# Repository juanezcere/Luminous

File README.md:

# Luminous
This is a PDB design to show information in a luminous screen

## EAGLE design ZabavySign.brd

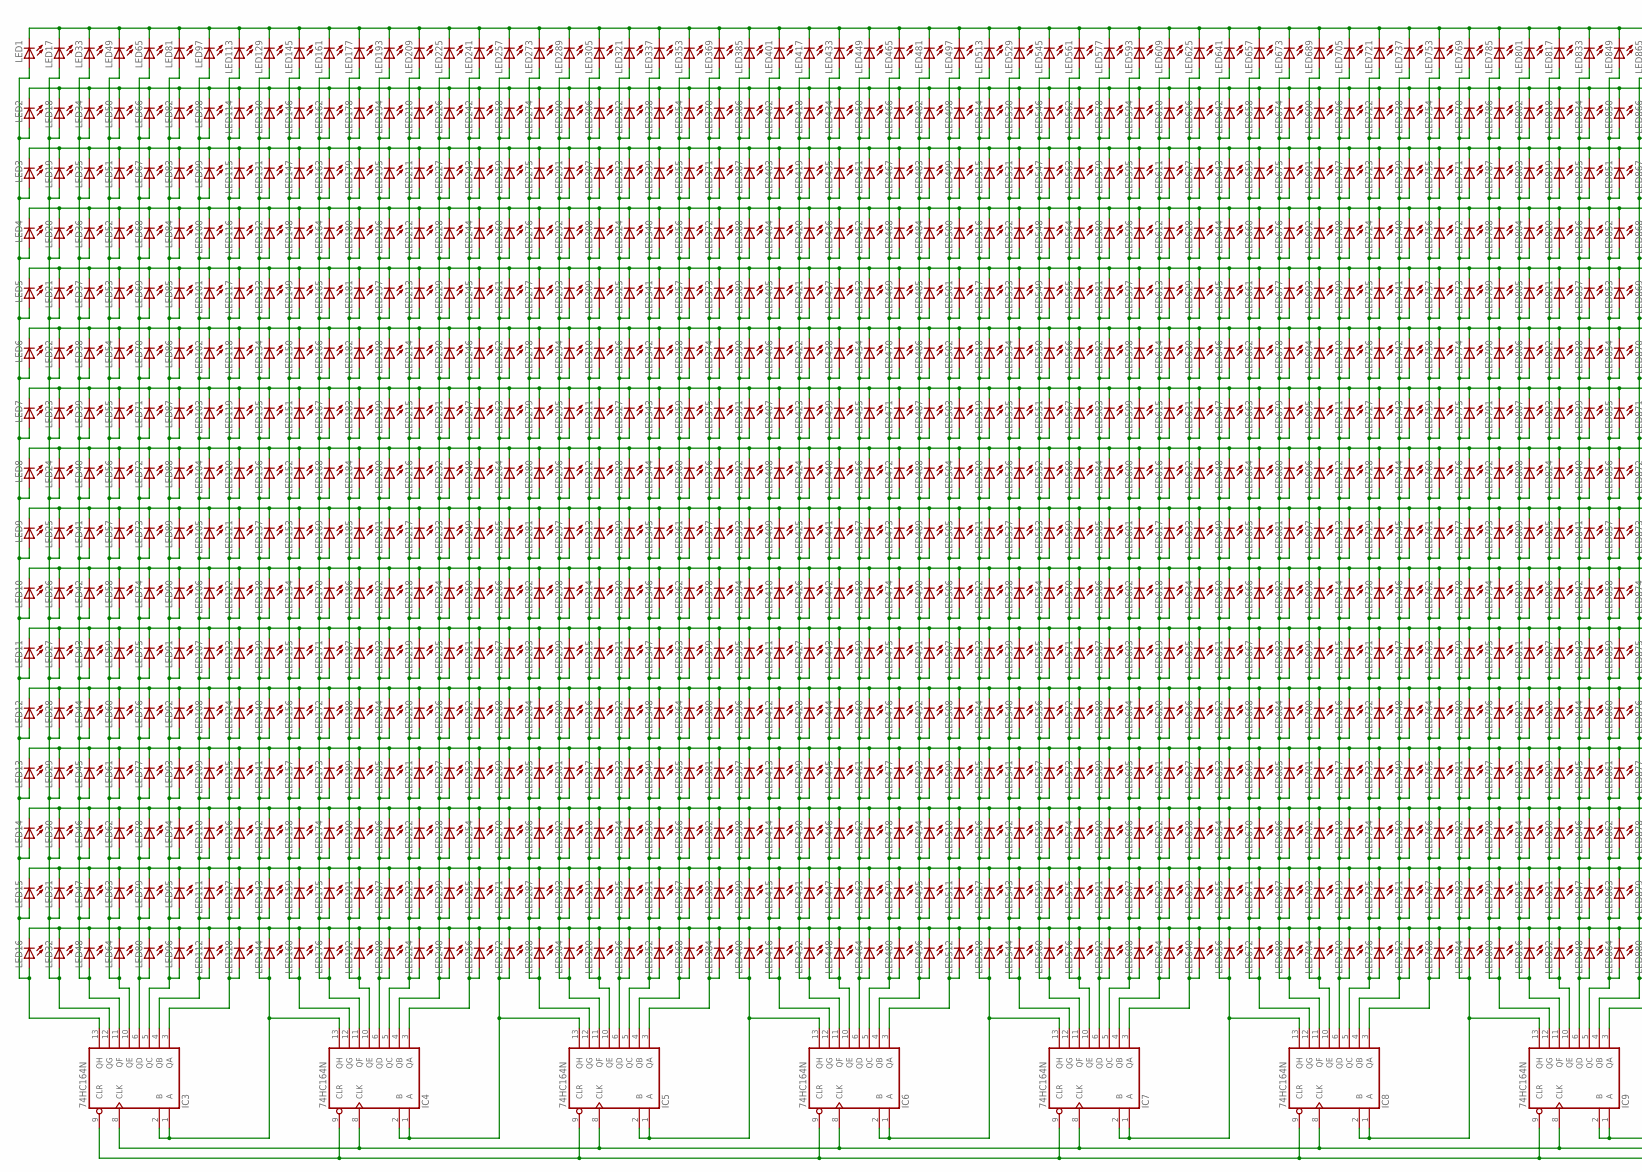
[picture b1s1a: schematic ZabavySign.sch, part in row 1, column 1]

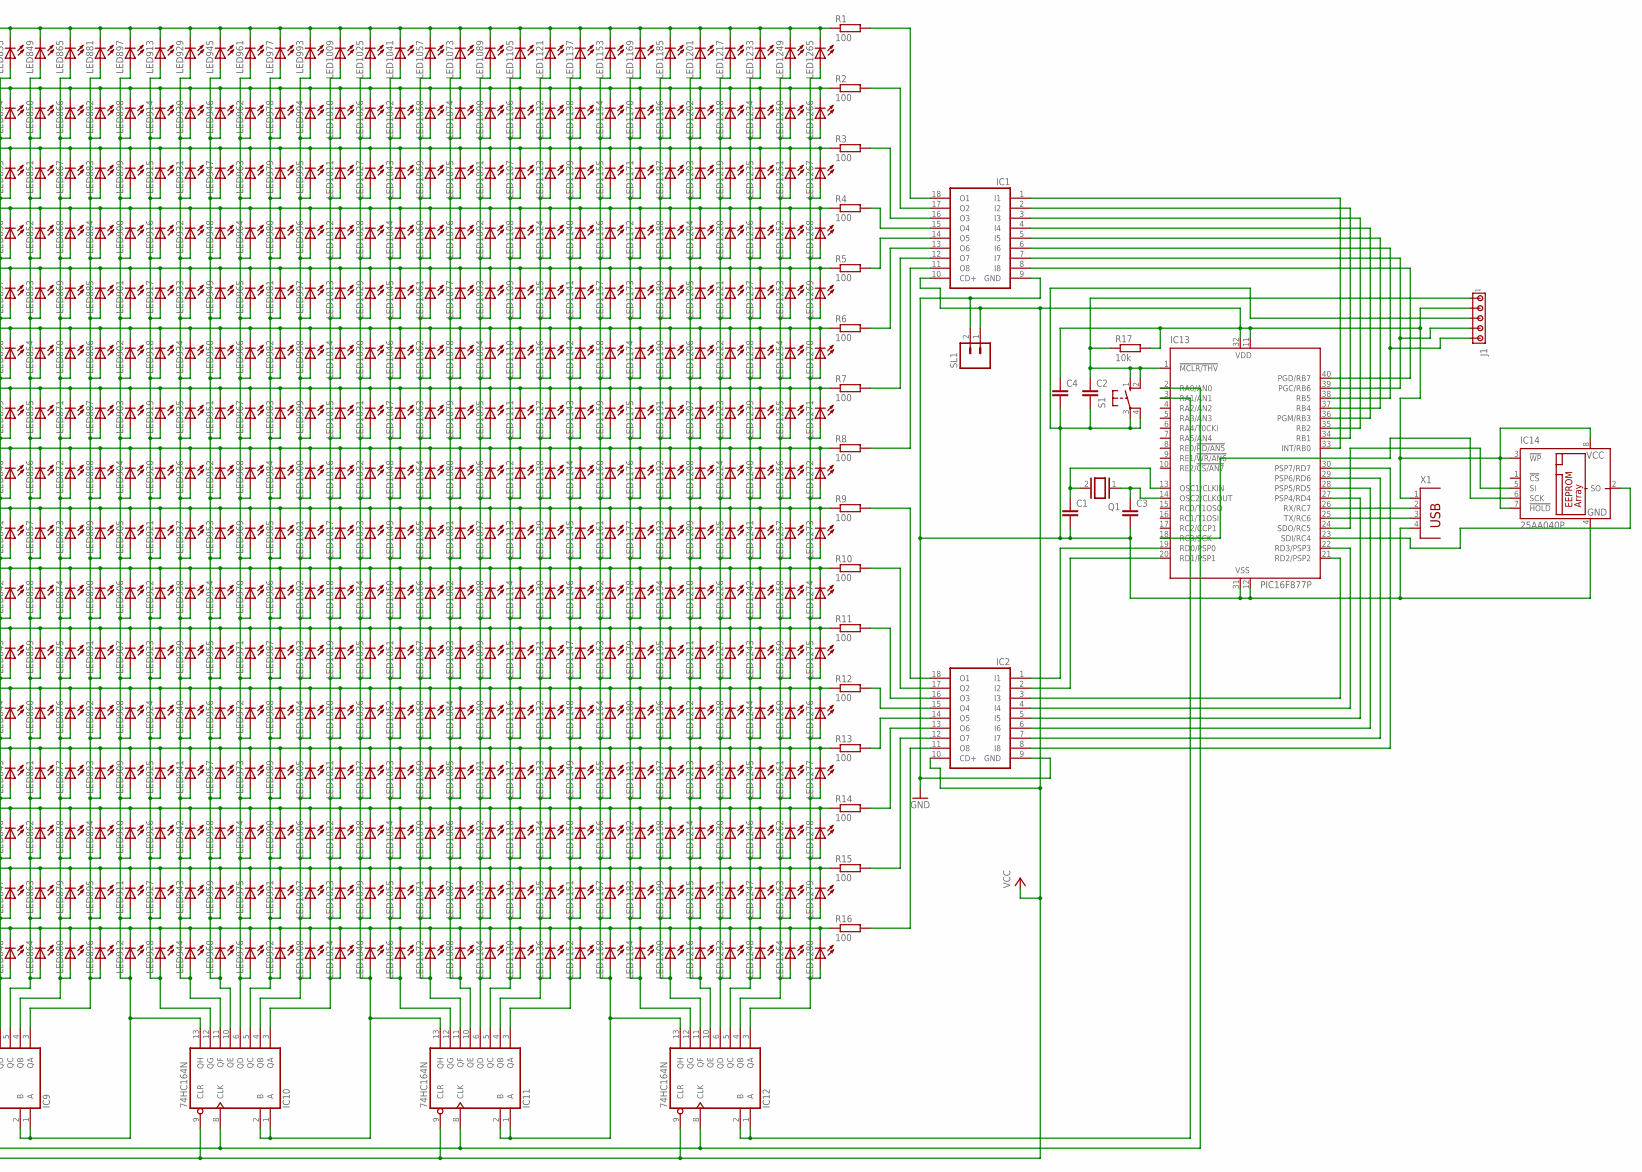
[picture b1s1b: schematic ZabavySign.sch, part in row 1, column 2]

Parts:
C1, C2, C3, C4: C-EU050-024X044; C050-024X044
IC1, IC2: ULN2803A; DIL18
IC3, IC4, IC5, IC6, IC7, IC8, IC9, IC10, IC11, IC12: 74HC164N; DIL14
IC13: PIC16F877P; DIL40
IC14: 25AA040P; DIL8
J1: MTA05-100; 10X05MTA
LED1, LED2, LED3, LED4, LED5, LED6, LED7, LED8, LED9, LED10, LED11, LED12, LED13, LED14, LED15, LED16, LED17, LED18, LED19, LED20, LED21, LED22, LED23, LED24, LED25, LED26, LED27, LED28, LED29, LED30, LED31, LED32, LED33, LED34, LED35, LED36, LED37, LED38, LED39, LED40, LED41, LED42, LED43, LED44, LED45, LED46, LED47, LED48, LED49, LED50, LED51, LED52, LED53, LED54, LED55, LED56, LED57, LED58, LED59, LED60, LED61, LED62, LED63, LED64, LED65, LED66, LED67, LED68, LED69, LED70, LED71, LED72, LED73, LED74, LED75, LED76, LED77, LED78, LED79, LED80, LED81, LED82, LED83, LED84, LED85, LED86, LED87, LED88, LED89, LED90, LED91, LED92, LED93, LED94, LED95, LED96, LED97, LED98, LED99, LED100, LED101, LED102, LED103, LED104, LED105, LED106, LED107, LED108, LED109, LED110, LED111, LED112, LED113, LED114, LED115, LED116, LED117, LED118, LED119, LED120, LED121, LED122, LED123, LED124, LED125, LED126, LED127, LED128, LED129, LED130, LED131, LED132, LED133, LED134, LED135, LED136, LED137, LED138, LED139, LED140, LED141, LED142, LED143, LED144, LED145, LED146, LED147, LED148, LED149, LED150, LED151, LED152, LED153, LED154, LED155, LED156, LED157, LED158, LED159, LED160, LED161, LED162, LED163, LED164, LED165, LED166, LED167, LED168, LED169, LED170, LED171, LED172, LED173, LED174, LED175, LED176, LED177, LED178, LED179, LED180, LED181, LED182, LED183, LED184, LED185, LED186, LED187, LED188, LED189, LED190, LED191, LED192, LED193, LED194, LED195, LED196, LED197, LED198, LED199, LED200, LED201, LED202, LED203, LED204, LED205, LED206, LED207, LED208, LED209, LED210, LED211, LED212, LED213, LED214, LED215, LED216, LED217, LED218, LED219, LED220, LED221, LED222, LED223, LED224, LED225, LED226, LED227, LED228, LED229, LED230, LED231, LED232, LED233, LED234, LED235, LED236, LED237, LED238, LED239, LED240, LED241, LED242, LED243, LED244, LED245, LED246, LED247, LED248, LED249, LED250, LED251, LED252, LED253, LED254, LED255, LED256, LED257, LED258, LED259, LED260, LED261, LED262, LED263, LED264, LED265, LED266, LED267, LED268, LED269, LED270, LED271, LED272, LED273, LED274, LED275, LED276, LED277, LED278, LED279, LED280, LED281, LED282, LED283, LED284, LED285, LED286, LED287, LED288, LED289, LED290, LED291, LED292, LED293, LED294, LED295, LED296, LED297, LED298, LED299, LED300, LED301, LED302, LED303, LED304, LED305, LED306, LED307, LED308, LED309, LED310, LED311, LED312, LED313, LED314, LED315, LED316, LED317, LED318, LED319, LED320, LED321, LED322, LED323, LED324, LED325, LED326, LED327, LED328, LED329, LED330, LED331, LED332, LED333, LED334, LED335, LED336, LED337, LED338, LED339, LED340, LED341, LED342, LED343, LED344, LED345, LED346, LED347, LED348, LED349, LED350, LED351, LED352, LED353, LED354, LED355, LED356, LED357, LED358, LED359, LED360, LED361, LED362, LED363, LED364, LED365, LED366, LED367, LED368, LED369, LED370, LED371, LED372, LED373, LED374, LED375, LED376, LED377, LED378, LED379, LED380, LED381, LED382, LED383, LED384, LED385, LED386, LED387, LED388, LED389, LED390, LED391, LED392, LED393, LED394, LED395, LED396, LED397, LED398, LED399, LED400, LED401, LED402, LED403, LED404, LED405, LED406, LED407, LED408, LED409, LED410, LED411, LED412, LED413, LED414, LED415, LED416, LED417, LED418, LED419, LED420, LED421, LED422, LED423, LED424, LED425, LED426, LED427, LED428, LED429, LED430, LED431, LED432, LED433, LED434, LED435, LED436, LED437, LED438, LED439, LED440, LED441, LED442, LED443, LED444, LED445, LED446, LED447, LED448, LED449, LED450, LED451, LED452, LED453, LED454, LED455, LED456, LED457, LED458, LED459, LED460, LED461, LED462, LED463, LED464, LED465, LED466, LED467, LED468, LED469, LED470, LED471, LED472, LED473, LED474, LED475, LED476, LED477, LED478, LED479, LED480, LED481, LED482, LED483, LED484, LED485, LED486, LED487, LED488, LED489, LED490, LED491, LED492, LED493, LED494, LED495, LED496, LED497, LED498, LED499, LED500, LED501, LED502, LED503, LED504, LED505, LED506, LED507, LED508, LED509, LED510, LED511, LED512, LED513, LED514, LED515, LED516, LED517, LED518, LED519, LED520, LED521, LED522, LED523, LED524, LED525, LED526, LED527, LED528, LED529, LED530, LED531, LED532, LED533, LED534, LED535, LED536, LED537, LED538, LED539, LED540, LED541, LED542, LED543, LED544, LED545, LED546, LED547, LED548, LED549, LED550, LED551, LED552, LED553, LED554, LED555, LED556, LED557, LED558, LED559, LED560, LED561, LED562, LED563, LED564, LED565, LED566, LED567, LED568, LED569, LED570, LED571, LED572, LED573, LED574, LED575, LED576, LED577, LED578, LED579, LED580, LED581, LED582, LED583, LED584, LED585, LED586, LED587, LED588, LED589, LED590, LED591, LED592, LED593, LED594, LED595, LED596, LED597, LED598, LED599, LED600, LED601, LED602, LED603, LED604, LED605, LED606, LED607, LED608, LED609, LED610, LED611, LED612, LED613, LED614, LED615, LED616, LED617, LED618, LED619, LED620, LED621, LED622, LED623, LED624, LED625, LED626, LED627, LED628, LED629, LED630, LED631, LED632, LED633, LED634, LED635, LED636, LED637, LED638, LED639, LED640, LED641, LED642, LED643, LED644, LED645, LED646, LED647, LED648, LED649, LED650, LED651, LED652, LED653, LED654, LED655, LED656, LED657, LED658, LED659, LED660, LED661, LED662, LED663, LED664, LED665, LED666, LED667, LED668, LED669, LED670, LED671, LED672, LED673, LED674, LED675, LED676, LED677, LED678, LED679, LED680, LED681, LED682, LED683, LED684, LED685, LED686, LED687, LED688, LED689, LED690, LED691, LED692, LED693, LED694, LED695, LED696, LED697, LED698, LED699, LED700, LED701, LED702, LED703, LED704, LED705, LED706, LED707, LED708, LED709, LED710, LED711, LED712, LED713, LED714, LED715, LED716, LED717, LED718, LED719, LED720, LED721, LED722, LED723, LED724, LED725, LED726, LED727, LED728, LED729, LED730, LED731, LED732, LED733, LED734, LED735, LED736, LED737, LED738, LED739, LED740, LED741, LED742, LED743, LED744, LED745, LED746, LED747, LED748, LED749, LED750, LED751, LED752, LED753, LED754, LED755, LED756, LED757, LED758, LED759, LED760, LED761, LED762, LED763, LED764, LED765, LED766, LED767, LED768, LED769, LED770, LED771, LED772, LED773, LED774, LED775, LED776, LED777, LED778, LED779, LED780, LED781, LED782, LED783, LED784, LED785, LED786, LED787, LED788, LED789, LED790, LED791, LED792, LED793, LED794, LED795, LED796, LED797, LED798, LED799, LED800, LED801, LED802, LED803, LED804, LED805, LED806, LED807, LED808, LED809, LED810, LED811, LED812, LED813, LED814, LED815, LED816, LED817, LED818, LED819, LED820, LED821, LED822, LED823, LED824, LED825, LED826, LED827, LED828, LED829, LED830, LED831, LED832, LED833, LED834, LED835, LED836, LED837, LED838, LED839, LED840, LED841, LED842, LED843, LED844, LED845, LED846, LED847, LED848, LED849, LED850, LED851, LED852, LED853, LED854, LED855, LED856, LED857, LED858, LED859, LED860, LED861, LED862, LED863, LED864, LED865, LED866, LED867, LED868, LED869, LED870, LED871, LED872, LED873, LED874, LED875, LED876, LED877, LED878, LED879, LED880, LED881, LED882, LED883, LED884, LED885, LED886, LED887, LED888, LED889, LED890, LED891, LED892, LED893, LED894, LED895, LED896, LED897, LED898, LED899, LED900, LED901, LED902, LED903, LED904, LED905, LED906, LED907, LED908, LED909, LED910, LED911, LED912, LED913, LED914, LED915, LED916, LED917, LED918, LED919, LED920, LED921, LED922, LED923, LED924, LED925, LED926, LED927, LED928, LED929, LED930, LED931, LED932, LED933, LED934, LED935, LED936, LED937, LED938, LED939, LED940, LED941, LED942, LED943, LED944, LED945, LED946, LED947, LED948, LED949, LED950, LED951, LED952, LED953, LED954, LED955, LED956, LED957, LED958, LED959, LED960, LED961, LED962, LED963, LED964, LED965, LED966, LED967, LED968, LED969, LED970, LED971, LED972, LED973, LED974, LED975, LED976, LED977, LED978, LED979, LED980, LED981, LED982, LED983, LED984, LED985, LED986, LED987, LED988, LED989, LED990, LED991, LED992, LED993, LED994, LED995, LED996, LED997, LED998, LED999, LED1000, LED1001, LED1002, LED1003, LED1004, LED1005, LED1006, LED1007, LED1008, LED1009, LED1010, LED1011, LED1012, LED1013, LED1014, LED1015, LED1016, LED1017, LED1018, LED1019, LED1020, LED1021, LED1022, LED1023, LED1024, LED1025, LED1026, LED1027, LED1028, LED1029, LED1030, LED1031, LED1032, LED1033, LED1034, LED1035, LED1036, LED1037, LED1038, LED1039, LED1040, LED1041, LED1042, LED1043, LED1044, LED1045, LED1046, LED1047, LED1048, LED1049, LED1050, LED1051, LED1052, LED1053, LED1054, LED1055, LED1056, LED1057, LED1058, LED1059, LED1060, LED1061, LED1062, LED1063, LED1064, LED1065, LED1066, LED1067, LED1068, LED1069, LED1070, LED1071, LED1072, LED1073, LED1074, LED1075, LED1076, LED1077, LED1078, LED1079, LED1080, LED1081, LED1082, LED1083, LED1084, LED1085, LED1086, LED1087, LED1088, LED1089, LED1090, LED1091, LED1092, LED1093, LED1094, LED1095, LED1096, LED1097, LED1098, LED1099, LED1100, LED1101, LED1102, LED1103, LED1104, LED1105, LED1106, LED1107, LED1108, LED1109, LED1110, LED1111, LED1112, LED1113, LED1114, LED1115, LED1116, LED1117, LED1118, LED1119, LED1120, LED1121, LED1122, LED1123, LED1124, LED1125, LED1126, LED1127, LED1128, LED1129, LED1130, LED1131, LED1132, LED1133, LED1134, LED1135, LED1136, LED1137, LED1138, LED1139, LED1140, LED1141, LED1142, LED1143, LED1144, LED1145, LED1146, LED1147, LED1148, LED1149, LED1150, LED1151, LED1152, LED1153, LED1154, LED1155, LED1156, LED1157, LED1158, LED1159, LED1160, LED1161, LED1162, LED1163, LED1164, LED1165, LED1166, LED1167, LED1168, LED1169, LED1170, LED1171, LED1172, LED1173, LED1174, LED1175, LED1176, LED1177, LED1178, LED1179, LED1180, LED1181, LED1182, LED1183, LED1184, LED1185, LED1186, LED1187, LED1188, LED1189, LED1190, LED1191, LED1192, LED1193, LED1194, LED1195, LED1196, LED1197, LED1198, LED1199, LED1200, LED1201, LED1202, LED1203, LED1204, LED1205, LED1206, LED1207, LED1208, LED1209, LED1210, LED1211, LED1212, LED1213, LED1214, LED1215, LED1216, LED1217, LED1218, LED1219, LED1220, LED1221, LED1222, LED1223, LED1224, LED1225, LED1226, LED1227, LED1228, LED1229, LED1230, LED1231, LED1232, LED1233, LED1234, LED1235, LED1236, LED1237, LED1238, LED1239, LED1240, LED1241, LED1242, LED1243, LED1244, LED1245, LED1246, LED1247, LED1248, LED1249, LED1250, LED1251, LED1252, LED1253, LED1254, LED1255, LED1256, LED1257, LED1258, LED1259, LED1260, LED1261, LED1262, LED1263, LED1264, LED1265, LED1266, LED1267, LED1268, LED1269, LED1270, LED1271, LED1272, LED1273, LED1274, LED1275, LED1276, LED1277, LED1278, LED1279, LED1280: LED5MM
Q1: XTAL/S; QS
R1, R2, R3, R4, R5, R6, R7, R8, R9, R10, R11, R12, R13, R14, R15, R16: 100; 0207/10
R17: 10k; 0207/10
S1: 10-XX; B3F-10XX
SL1: M02; 02P
X1: PN87520

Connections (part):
GND: C1.2, C2.2, C3.2, C4.2, IC1.9 (GND), IC2.9 (GND), IC3.7 (GND), IC4.7 (GND), IC5.7 (GND), IC6.7 (GND), IC7.7 (GND), IC8.7 (GND), IC9.7 (GND), IC10.7 (GND), IC11.7 (GND), IC12.7 (GND), IC13.12 (VSS), IC13.31 (VSS), IC14.4 (GND), J1.3, S1.3, S1.4 (P1), SL1.2, X1.4
unnamed: C1.1, IC13.13 (OSC1/CLKIN), Q1.2
unnamed: IC3.12 (QG), LED17.A, LED18.A, LED19.A, LED20.A, LED21.A, LED22.A, LED23.A, LED24.A, LED25.A, LED26.A, LED27.A, LED28.A, LED29.A, LED30.A, LED31.A, LED32.A
unnamed: IC3.11 (QF), LED33.A, LED34.A, LED35.A, LED36.A, LED37.A, LED38.A, LED39.A, LED40.A, LED41.A, LED42.A, LED43.A, LED44.A, LED45.A, LED46.A, LED47.A, LED48.A
unnamed: IC3.10 (QE), LED49.A, LED50.A, LED51.A, LED52.A, LED53.A, LED54.A, LED55.A, LED56.A, LED57.A, LED58.A, LED59.A, LED60.A, LED61.A, LED62.A, LED63.A, LED64.A
unnamed: IC3.6 (QD), LED65.A, LED66.A, LED67.A, LED68.A, LED69.A, LED70.A, LED71.A, LED72.A, LED73.A, LED74.A, LED75.A, LED76.A, LED77.A, LED78.A, LED79.A, LED80.A
unnamed: IC3.5 (QC), LED81.A, LED82.A, LED83.A, LED84.A, LED85.A, LED86.A, LED87.A, LED88.A, LED89.A, LED90.A, LED91.A, LED92.A, LED93.A, LED94.A, LED95.A, LED96.A
unnamed: IC3.4 (QB), LED97.A, LED98.A, LED99.A, LED100.A, LED101.A, LED102.A, LED103.A, LED104.A, LED105.A, LED106.A, LED107.A, LED108.A, LED109.A, LED110.A, LED111.A, LED112.A
unnamed: IC3.3 (QA), LED113.A, LED114.A, LED115.A, LED116.A, LED117.A, LED118.A, LED119.A, LED120.A, LED121.A, LED122.A, LED123.A, LED124.A, LED125.A, LED126.A, LED127.A, LED128.A
unnamed: IC3.1 (A), IC3.2 (B), IC4.13 (QH), LED129.A, LED130.A, LED131.A, LED132.A, LED133.A, LED134.A, LED135.A, LED136.A, LED137.A, LED138.A, LED139.A, LED140.A, LED141.A, LED142.A, LED143.A, LED144.A
unnamed: IC4.12 (QG), LED145.A, LED146.A, LED147.A, LED148.A, LED149.A, LED150.A, LED151.A, LED152.A, LED153.A, LED154.A, LED155.A, LED156.A, LED157.A, LED158.A, LED159.A, LED160.A
unnamed: IC3.13 (QH), LED1.A, LED2.A, LED3.A, LED4.A, LED5.A, LED6.A, LED7.A, LED8.A, LED9.A, LED10.A, LED11.A, LED12.A, LED13.A, LED14.A, LED15.A, LED16.A
unnamed: IC4.11 (QF), LED161.A, LED162.A, LED163.A, LED164.A, LED165.A, LED166.A, LED167.A, LED168.A, LED169.A, LED170.A, LED171.A, LED172.A, LED173.A, LED174.A, LED175.A, LED176.A
unnamed: IC4.10 (QE), LED177.A, LED178.A, LED179.A, LED180.A, LED181.A, LED182.A, LED183.A, LED184.A, LED185.A, LED186.A, LED187.A, LED188.A, LED189.A, LED190.A, LED191.A, LED192.A
unnamed: IC4.6 (QD), LED193.A, LED194.A, LED195.A, LED196.A, LED197.A, LED198.A, LED199.A, LED200.A, LED201.A, LED202.A, LED203.A, LED204.A, LED205.A, LED206.A, LED207.A, LED208.A
unnamed: IC4.5 (QC), LED209.A, LED210.A, LED211.A, LED212.A, LED213.A, LED214.A, LED215.A, LED216.A, LED217.A, LED218.A, LED219.A, LED220.A, LED221.A, LED222.A, LED223.A, LED224.A
unnamed: IC4.4 (QB), LED225.A, LED226.A, LED227.A, LED228.A, LED229.A, LED230.A, LED231.A, LED232.A, LED233.A, LED234.A, LED235.A, LED236.A, LED237.A, LED238.A, LED239.A, LED240.A
unnamed: IC4.3 (QA), LED241.A, LED242.A, LED243.A, LED244.A, LED245.A, LED246.A, LED247.A, LED248.A, LED249.A, LED250.A, LED251.A, LED252.A, LED253.A, LED254.A, LED255.A, LED256.A
unnamed: C3.1, IC13.14 (OSC2/CLKOUT), Q1.1
unnamed: IC5.12 (QG), LED273.A, LED274.A, LED275.A, LED276.A, LED277.A, LED278.A, LED279.A, LED280.A, LED281.A, LED282.A, LED283.A, LED284.A, LED285.A, LED286.A, LED287.A, LED288.A
unnamed: IC5.11 (QF), LED289.A, LED290.A, LED291.A, LED292.A, LED293.A, LED294.A, LED295.A, LED296.A, LED297.A, LED298.A, LED299.A, LED300.A, LED301.A, LED302.A, LED303.A, LED304.A
unnamed: IC5.10 (QE), LED305.A, LED306.A, LED307.A, LED308.A, LED309.A, LED310.A, LED311.A, LED312.A, LED313.A, LED314.A, LED315.A, LED316.A, LED317.A, LED318.A, LED319.A, LED320.A
unnamed: IC5.6 (QD), LED321.A, LED322.A, LED323.A, LED324.A, LED325.A, LED326.A, LED327.A, LED328.A, LED329.A, LED330.A, LED331.A, LED332.A, LED333.A, LED334.A, LED335.A, LED336.A
unnamed: IC5.5 (QC), LED337.A, LED338.A, LED339.A, LED340.A, LED341.A, LED342.A, LED343.A, LED344.A, LED345.A, LED346.A, LED347.A, LED348.A, LED349.A, LED350.A, LED351.A, LED352.A
unnamed: IC5.4 (QB), LED353.A, LED354.A, LED355.A, LED356.A, LED357.A, LED358.A, LED359.A, LED360.A, LED361.A, LED362.A, LED363.A, LED364.A, LED365.A, LED366.A, LED367.A, LED368.A
unnamed: IC5.3 (QA), LED369.A, LED370.A, LED371.A, LED372.A, LED373.A, LED374.A, LED375.A, LED376.A, LED377.A, LED378.A, LED379.A, LED380.A, LED381.A, LED382.A, LED383.A, LED384.A
unnamed: IC12.1 (A), IC12.2 (B), IC13.3 (RA1/AN1)
unnamed: IC6.12 (QG), LED401.A, LED402.A, LED403.A, LED404.A, LED405.A, LED406.A, LED407.A, LED408.A, LED409.A, LED410.A, LED411.A, LED412.A, LED413.A, LED414.A, LED415.A, LED416.A
unnamed: IC6.11 (QF), LED417.A, LED418.A, LED419.A, LED420.A, LED421.A, LED422.A, LED423.A, LED424.A, LED425.A, LED426.A, LED427.A, LED428.A, LED429.A, LED430.A, LED431.A, LED432.A
unnamed: IC6.10 (QE), LED433.A, LED434.A, LED435.A, LED436.A, LED437.A, LED438.A, LED439.A, LED440.A, LED441.A, LED442.A, LED443.A, LED444.A, LED445.A, LED446.A, LED447.A, LED448.A
unnamed: IC6.6 (QD), LED449.A, LED450.A, LED451.A, LED452.A, LED453.A, LED454.A, LED455.A, LED456.A, LED457.A, LED458.A, LED459.A, LED460.A, LED461.A, LED462.A, LED463.A, LED464.A
unnamed: IC6.5 (QC), LED465.A, LED466.A, LED467.A, LED468.A, LED469.A, LED470.A, LED471.A, LED472.A, LED473.A, LED474.A, LED475.A, LED476.A, LED477.A, LED478.A, LED479.A, LED480.A
unnamed: IC6.4 (QB), LED481.A, LED482.A, LED483.A, LED484.A, LED485.A, LED486.A, LED487.A, LED488.A, LED489.A, LED490.A, LED491.A, LED492.A, LED493.A, LED494.A, LED495.A, LED496.A
unnamed: IC6.3 (QA), LED497.A, LED498.A, LED499.A, LED500.A, LED501.A, LED502.A, LED503.A, LED504.A, LED505.A, LED506.A, LED507.A, LED508.A, LED509.A, LED510.A, LED511.A, LED512.A
unnamed: IC7.12 (QG), LED529.A, LED530.A, LED531.A, LED532.A, LED533.A, LED534.A, LED535.A, LED536.A, LED537.A, LED538.A, LED539.A, LED540.A, LED541.A, LED542.A, LED543.A, LED544.A
unnamed: IC7.11 (QF), LED545.A, LED546.A, LED547.A, LED548.A, LED549.A, LED550.A, LED551.A, LED552.A, LED553.A, LED554.A, LED555.A, LED556.A, LED557.A, LED558.A, LED559.A, LED560.A
unnamed: IC7.10 (QE), LED561.A, LED562.A, LED563.A, LED564.A, LED565.A, LED566.A, LED567.A, LED568.A, LED569.A, LED570.A, LED571.A, LED572.A, LED573.A, LED574.A, LED575.A, LED576.A
unnamed: IC7.6 (QD), LED577.A, LED578.A, LED579.A, LED580.A, LED581.A, LED582.A, LED583.A, LED584.A, LED585.A, LED586.A, LED587.A, LED588.A, LED589.A, LED590.A, LED591.A, LED592.A
unnamed: IC7.5 (QC), LED593.A, LED594.A, LED595.A, LED596.A, LED597.A, LED598.A, LED599.A, LED600.A, LED601.A, LED602.A, LED603.A, LED604.A, LED605.A, LED606.A, LED607.A, LED608.A
unnamed: IC7.4 (QB), LED609.A, LED610.A, LED611.A, LED612.A, LED613.A, LED614.A, LED615.A, LED616.A, LED617.A, LED618.A, LED619.A, LED620.A, LED621.A, LED622.A, LED623.A, LED624.A
unnamed: IC7.3 (QA), LED625.A, LED626.A, LED627.A, LED628.A, LED629.A, LED630.A, LED631.A, LED632.A, LED633.A, LED634.A, LED635.A, LED636.A, LED637.A, LED638.A, LED639.A, LED640.A
unnamed: IC8.12 (QG), LED657.A, LED658.A, LED659.A, LED660.A, LED661.A, LED662.A, LED663.A, LED664.A, LED665.A, LED666.A, LED667.A, LED668.A, LED669.A, LED670.A, LED671.A, LED672.A
unnamed: IC8.11 (QF), LED673.A, LED674.A, LED675.A, LED676.A, LED677.A, LED678.A, LED679.A, LED680.A, LED681.A, LED682.A, LED683.A, LED684.A, LED685.A, LED686.A, LED687.A, LED688.A
unnamed: IC8.10 (QE), LED689.A, LED690.A, LED691.A, LED692.A, LED693.A, LED694.A, LED695.A, LED696.A, LED697.A, LED698.A, LED699.A, LED700.A, LED701.A, LED702.A, LED703.A, LED704.A
unnamed: IC8.6 (QD), LED705.A, LED706.A, LED707.A, LED708.A, LED709.A, LED710.A, LED711.A, LED712.A, LED713.A, LED714.A, LED715.A, LED716.A, LED717.A, LED718.A, LED719.A, LED720.A
unnamed: IC8.5 (QC), LED721.A, LED722.A, LED723.A, LED724.A, LED725.A, LED726.A, LED727.A, LED728.A, LED729.A, LED730.A, LED731.A, LED732.A, LED733.A, LED734.A, LED735.A, LED736.A
unnamed: IC8.4 (QB), LED737.A, LED738.A, LED739.A, LED740.A, LED741.A, LED742.A, LED743.A, LED744.A, LED745.A, LED746.A, LED747.A, LED748.A, LED749.A, LED750.A, LED751.A, LED752.A
unnamed: IC8.3 (QA), LED753.A, LED754.A, LED755.A, LED756.A, LED757.A, LED758.A, LED759.A, LED760.A, LED761.A, LED762.A, LED763.A, LED764.A, LED765.A, LED766.A, LED767.A, LED768.A
unnamed: IC2.1 (I1), IC13.19 (RD0/PSP0)
unnamed: IC9.12 (QG), LED785.A, LED786.A, LED787.A, LED788.A, LED789.A, LED790.A, LED791.A, LED792.A, LED793.A, LED794.A, LED795.A, LED796.A, LED797.A, LED798.A, LED799.A, LED800.A
unnamed: IC2.2 (I2), IC13.20 (RD1/PSP1)
unnamed: IC9.10 (QE), LED817.A, LED818.A, LED819.A, LED820.A, LED821.A, LED822.A, LED823.A, LED824.A, LED825.A, LED826.A, LED827.A, LED828.A, LED829.A, LED830.A, LED831.A, LED832.A
unnamed: IC9.6 (QD), LED833.A, LED834.A, LED835.A, LED836.A, LED837.A, LED838.A, LED839.A, LED840.A, LED841.A, LED842.A, LED843.A, LED844.A, LED845.A, LED846.A, LED847.A, LED848.A
unnamed: IC9.5 (QC), LED849.A, LED850.A, LED851.A, LED852.A, LED853.A, LED854.A, LED855.A, LED856.A, LED857.A, LED858.A, LED859.A, LED860.A, LED861.A, LED862.A, LED863.A, LED864.A
unnamed: IC9.4 (QB), LED865.A, LED866.A, LED867.A, LED868.A, LED869.A, LED870.A, LED871.A, LED872.A, LED873.A, LED874.A, LED875.A, LED876.A, LED877.A, LED878.A, LED879.A, LED880.A
unnamed: IC9.3 (QA), LED881.A, LED882.A, LED883.A, LED884.A, LED885.A, LED886.A, LED887.A, LED888.A, LED889.A, LED890.A, LED891.A, LED892.A, LED893.A, LED894.A, LED895.A, LED896.A
unnamed: IC2.3 (I3), IC13.21 (RD2/PSP2)
unnamed: IC10.12 (QG), LED913.A, LED914.A, LED915.A, LED916.A, LED917.A, LED918.A, LED919.A, LED920.A, LED921.A, LED922.A, LED923.A, LED924.A, LED925.A, LED926.A, LED927.A, LED928.A
unnamed: IC10.11 (QF), LED929.A, LED930.A, LED931.A, LED932.A, LED933.A, LED934.A, LED935.A, LED936.A, LED937.A, LED938.A, LED939.A, LED940.A, LED941.A, LED942.A, LED943.A, LED944.A
unnamed: IC10.10 (QE), LED945.A, LED946.A, LED947.A, LED948.A, LED949.A, LED950.A, LED951.A, LED952.A, LED953.A, LED954.A, LED955.A, LED956.A, LED957.A, LED958.A, LED959.A, LED960.A
unnamed: IC10.6 (QD), LED961.A, LED962.A, LED963.A, LED964.A, LED965.A, LED966.A, LED967.A, LED968.A, LED969.A, LED970.A, LED971.A, LED972.A, LED973.A, LED974.A, LED975.A, LED976.A
unnamed: IC10.5 (QC), LED977.A, LED978.A, LED979.A, LED980.A, LED981.A, LED982.A, LED983.A, LED984.A, LED985.A, LED986.A, LED987.A, LED988.A, LED989.A, LED990.A, LED991.A, LED992.A
unnamed: IC10.4 (QB), LED993.A, LED994.A, LED995.A, LED996.A, LED997.A, LED998.A, LED999.A, LED1000.A, LED1001.A, LED1002.A, LED1003.A, LED1004.A, LED1005.A, LED1006.A, LED1007.A, LED1008.A
unnamed: IC10.3 (QA), LED1009.A, LED1010.A, LED1011.A, LED1012.A, LED1013.A, LED1014.A, LED1015.A, LED1016.A, LED1017.A, LED1018.A, LED1019.A, LED1020.A, LED1021.A, LED1022.A, LED1023.A, LED1024.A
unnamed: IC2.4 (I4), IC13.22 (RD3/PSP3)
unnamed: IC11.12 (QG), LED1041.A, LED1042.A, LED1043.A, LED1044.A, LED1045.A, LED1046.A, LED1047.A, LED1048.A, LED1049.A, LED1050.A, LED1051.A, LED1052.A, LED1053.A, LED1054.A, LED1055.A, LED1056.A
unnamed: IC11.11 (QF), LED1057.A, LED1058.A, LED1059.A, LED1060.A, LED1061.A, LED1062.A, LED1063.A, LED1064.A, LED1065.A, LED1066.A, LED1067.A, LED1068.A, LED1069.A, LED1070.A, LED1071.A, LED1072.A
unnamed: IC11.10 (QE), LED1073.A, LED1074.A, LED1075.A, LED1076.A, LED1077.A, LED1078.A, LED1079.A, LED1080.A, LED1081.A, LED1082.A, LED1083.A, LED1084.A, LED1085.A, LED1086.A, LED1087.A, LED1088.A
unnamed: IC11.6 (QD), LED1089.A, LED1090.A, LED1091.A, LED1092.A, LED1093.A, LED1094.A, LED1095.A, LED1096.A, LED1097.A, LED1098.A, LED1099.A, LED1100.A, LED1101.A, LED1102.A, LED1103.A, LED1104.A
unnamed: IC11.5 (QC), LED1105.A, LED1106.A, LED1107.A, LED1108.A, LED1109.A, LED1110.A, LED1111.A, LED1112.A, LED1113.A, LED1114.A, LED1115.A, LED1116.A, LED1117.A, LED1118.A, LED1119.A, LED1120.A
unnamed: IC11.4 (QB), LED1121.A, LED1122.A, LED1123.A, LED1124.A, LED1125.A, LED1126.A, LED1127.A, LED1128.A, LED1129.A, LED1130.A, LED1131.A, LED1132.A, LED1133.A, LED1134.A, LED1135.A, LED1136.A
unnamed: IC11.3 (QA), LED1137.A, LED1138.A, LED1139.A, LED1140.A, LED1141.A, LED1142.A, LED1143.A, LED1144.A, LED1145.A, LED1146.A, LED1147.A, LED1148.A, LED1149.A, LED1150.A, LED1151.A, LED1152.A
unnamed: IC2.5 (I5), IC13.27 (PSP4/RD4)
unnamed: IC12.12 (QG), LED1169.A, LED1170.A, LED1171.A, LED1172.A, LED1173.A, LED1174.A, LED1175.A, LED1176.A, LED1177.A, LED1178.A, LED1179.A, LED1180.A, LED1181.A, LED1182.A, LED1183.A, LED1184.A
unnamed: IC12.11 (QF), LED1185.A, LED1186.A, LED1187.A, LED1188.A, LED1189.A, LED1190.A, LED1191.A, LED1192.A, LED1193.A, LED1194.A, LED1195.A, LED1196.A, LED1197.A, LED1198.A, LED1199.A, LED1200.A
unnamed: IC12.10 (QE), LED1201.A, LED1202.A, LED1203.A, LED1204.A, LED1205.A, LED1206.A, LED1207.A, LED1208.A, LED1209.A, LED1210.A, LED1211.A, LED1212.A, LED1213.A, LED1214.A, LED1215.A, LED1216.A
unnamed: IC12.6 (QD), LED1217.A, LED1218.A, LED1219.A, LED1220.A, LED1221.A, LED1222.A, LED1223.A, LED1224.A, LED1225.A, LED1226.A, LED1227.A, LED1228.A, LED1229.A, LED1230.A, LED1231.A, LED1232.A
unnamed: IC12.5 (QC), LED1233.A, LED1234.A, LED1235.A, LED1236.A, LED1237.A, LED1238.A, LED1239.A, LED1240.A, LED1241.A, LED1242.A, LED1243.A, LED1244.A, LED1245.A, LED1246.A, LED1247.A, LED1248.A
unnamed: IC12.4 (QB), LED1249.A, LED1250.A, LED1251.A, LED1252.A, LED1253.A, LED1254.A, LED1255.A, LED1256.A, LED1257.A, LED1258.A, LED1259.A, LED1260.A, LED1261.A, LED1262.A, LED1263.A, LED1264.A
unnamed: IC12.3 (QA), LED1265.A, LED1266.A, LED1267.A, LED1268.A, LED1269.A, LED1270.A, LED1271.A, LED1272.A, LED1273.A, LED1274.A, LED1275.A, LED1276.A, LED1277.A, LED1278.A, LED1279.A, LED1280.A
unnamed: LED1.K (C), LED17.K (C), LED33.K (C), LED49.K (C), LED65.K (C), LED81.K (C), LED97.K (C), LED113.K (C), LED129.K (C), LED145.K (C), LED161.K (C), LED177.K (C), LED193.K (C), LED209.K (C), LED225.K (C), LED241.K (C), LED257.K (C), LED273.K (C), LED289.K (C), LED305.K (C), LED321.K (C), LED337.K (C), LED353.K (C), LED369.K (C), LED385.K (C), LED401.K (C), LED417.K (C), LED433.K (C), LED449.K (C), LED465.K (C), LED481.K (C), LED497.K (C), LED513.K (C), LED529.K (C), LED545.K (C), LED561.K (C), LED577.K (C), LED593.K (C), LED609.K (C), LED625.K (C), LED641.K (C), LED657.K (C), LED673.K (C), LED689.K (C), LED705.K (C), LED721.K (C), LED737.K (C), LED753.K (C), LED769.K (C), LED785.K (C), LED801.K (C), LED817.K (C), LED833.K (C), LED849.K (C), LED865.K (C), LED881.K (C), LED897.K (C), LED913.K (C), LED929.K (C), LED945.K (C), LED961.K (C), LED977.K (C), LED993.K (C), LED1009.K (C), LED1025.K (C), LED1041.K (C), LED1057.K (C), LED1073.K (C), LED1089.K (C), LED1105.K (C), LED1121.K (C), LED1137.K (C), LED1153.K (C), LED1169.K (C), LED1185.K (C), LED1201.K (C), LED1217.K (C), LED1233.K (C), LED1249.K (C), LED1265.K (C), R1.1
unnamed: LED2.K (C), LED18.K (C), LED34.K (C), LED50.K (C), LED66.K (C), LED82.K (C), LED98.K (C), LED114.K (C), LED130.K (C), LED146.K (C), LED162.K (C), LED178.K (C), LED194.K (C), LED210.K (C), LED226.K (C), LED242.K (C), LED258.K (C), LED274.K (C), LED290.K (C), LED306.K (C), LED322.K (C), LED338.K (C), LED354.K (C), LED370.K (C), LED386.K (C), LED402.K (C), LED418.K (C), LED434.K (C), LED450.K (C), LED466.K (C), LED482.K (C), LED498.K (C), LED514.K (C), LED530.K (C), LED546.K (C), LED562.K (C), LED578.K (C), LED594.K (C), LED610.K (C), LED626.K (C), LED642.K (C), LED658.K (C), LED674.K (C), LED690.K (C), LED706.K (C), LED722.K (C), LED738.K (C), LED754.K (C), LED770.K (C), LED786.K (C), LED802.K (C), LED818.K (C), LED834.K (C), LED850.K (C), LED866.K (C), LED882.K (C), LED898.K (C), LED914.K (C), LED930.K (C), LED946.K (C), LED962.K (C), LED978.K (C), LED994.K (C), LED1010.K (C), LED1026.K (C), LED1042.K (C), LED1058.K (C), LED1074.K (C), LED1090.K (C), LED1106.K (C), LED1122.K (C), LED1138.K (C), LED1154.K (C), LED1170.K (C), LED1186.K (C), LED1202.K (C), LED1218.K (C), LED1234.K (C), LED1250.K (C), LED1266.K (C), R2.1
unnamed: LED3.K (C), LED19.K (C), LED35.K (C), LED51.K (C), LED67.K (C), LED83.K (C), LED99.K (C), LED115.K (C), LED131.K (C), LED147.K (C), LED163.K (C), LED179.K (C), LED195.K (C), LED211.K (C), LED227.K (C), LED243.K (C), LED259.K (C), LED275.K (C), LED291.K (C), LED307.K (C), LED323.K (C), LED339.K (C), LED355.K (C), LED371.K (C), LED387.K (C), LED403.K (C), LED419.K (C), LED435.K (C), LED451.K (C), LED467.K (C), LED483.K (C), LED499.K (C), LED515.K (C), LED531.K (C), LED547.K (C), LED563.K (C), LED579.K (C), LED595.K (C), LED611.K (C), LED627.K (C), LED643.K (C), LED659.K (C), LED675.K (C), LED691.K (C), LED707.K (C), LED723.K (C), LED739.K (C), LED755.K (C), LED771.K (C), LED787.K (C), LED803.K (C), LED819.K (C), LED835.K (C), LED851.K (C), LED867.K (C), LED883.K (C), LED899.K (C), LED915.K (C), LED931.K (C), LED947.K (C), LED963.K (C), LED979.K (C), LED995.K (C), LED1011.K (C), LED1027.K (C), LED1043.K (C), LED1059.K (C), LED1075.K (C), LED1091.K (C), LED1107.K (C), LED1123.K (C), LED1139.K (C), LED1155.K (C), LED1171.K (C), LED1187.K (C), LED1203.K (C), LED1219.K (C), LED1235.K (C), LED1251.K (C), LED1267.K (C), R3.1
unnamed: IC1.18 (O1), R1.2
unnamed: IC1.17 (O2), R2.2
unnamed: IC1.16 (O3), R3.2
unnamed: LED7.K (C), LED23.K (C), LED39.K (C), LED55.K (C), LED71.K (C), LED87.K (C), LED103.K (C), LED119.K (C), LED135.K (C), LED151.K (C), LED167.K (C), LED183.K (C), LED199.K (C), LED215.K (C), LED231.K (C), LED247.K (C), LED263.K (C), LED279.K (C), LED295.K (C), LED311.K (C), LED327.K (C), LED343.K (C), LED359.K (C), LED375.K (C), LED391.K (C), LED407.K (C), LED423.K (C), LED439.K (C), LED455.K (C), LED471.K (C), LED487.K (C), LED503.K (C), LED519.K (C), LED535.K (C), LED551.K (C), LED567.K (C), LED583.K (C), LED599.K (C), LED615.K (C), LED631.K (C), LED647.K (C), LED663.K (C), LED679.K (C), LED695.K (C), LED711.K (C), LED727.K (C), LED743.K (C), LED759.K (C), LED775.K (C), LED791.K (C), LED807.K (C), LED823.K (C), LED839.K (C), LED855.K (C), LED871.K (C), LED887.K (C), LED903.K (C), LED919.K (C), LED935.K (C), LED951.K (C), LED967.K (C), LED983.K (C), LED999.K (C), LED1015.K (C), LED1031.K (C), LED1047.K (C), LED1063.K (C), LED1079.K (C), LED1095.K (C), LED1111.K (C), LED1127.K (C), LED1143.K (C), LED1159.K (C), LED1175.K (C), LED1191.K (C), LED1207.K (C), LED1223.K (C), LED1239.K (C), LED1255.K (C), LED1271.K (C), R7.1
unnamed: IC1.15 (O4), R4.2
unnamed: IC1.14 (O5), R5.2
unnamed: IC1.13 (O6), R6.2
unnamed: LED4.K (C), LED20.K (C), LED36.K (C), LED52.K (C), LED68.K (C), LED84.K (C), LED100.K (C), LED116.K (C), LED132.K (C), LED148.K (C), LED164.K (C), LED180.K (C), LED196.K (C), LED212.K (C), LED228.K (C), LED244.K (C), LED260.K (C), LED276.K (C), LED292.K (C), LED308.K (C), LED324.K (C), LED340.K (C), LED356.K (C), LED372.K (C), LED388.K (C), LED404.K (C), LED420.K (C), LED436.K (C), LED452.K (C), LED468.K (C), LED484.K (C), LED500.K (C), LED516.K (C), LED532.K (C), LED548.K (C), LED564.K (C), LED580.K (C), LED596.K (C), LED612.K (C), LED628.K (C), LED644.K (C), LED660.K (C), LED676.K (C), LED692.K (C), LED708.K (C), LED724.K (C), LED740.K (C), LED756.K (C), LED772.K (C), LED788.K (C), LED804.K (C), LED820.K (C), LED836.K (C), LED852.K (C), LED868.K (C), LED884.K (C), LED900.K (C), LED916.K (C), LED932.K (C), LED948.K (C), LED964.K (C), LED980.K (C), LED996.K (C), LED1012.K (C), LED1028.K (C), LED1044.K (C), LED1060.K (C), LED1076.K (C), LED1092.K (C), LED1108.K (C), LED1124.K (C), LED1140.K (C), LED1156.K (C), LED1172.K (C), LED1188.K (C), LED1204.K (C), LED1220.K (C), LED1236.K (C), LED1252.K (C), LED1268.K (C), R4.1
unnamed: LED5.K (C), LED21.K (C), LED37.K (C), LED53.K (C), LED69.K (C), LED85.K (C), LED101.K (C), LED117.K (C), LED133.K (C), LED149.K (C), LED165.K (C), LED181.K (C), LED197.K (C), LED213.K (C), LED229.K (C), LED245.K (C), LED261.K (C), LED277.K (C), LED293.K (C), LED309.K (C), LED325.K (C), LED341.K (C), LED357.K (C), LED373.K (C), LED389.K (C), LED405.K (C), LED421.K (C), LED437.K (C), LED453.K (C), LED469.K (C), LED485.K (C), LED501.K (C), LED517.K (C), LED533.K (C), LED549.K (C), LED565.K (C), LED581.K (C), LED597.K (C), LED613.K (C), LED629.K (C), LED645.K (C), LED661.K (C), LED677.K (C), LED693.K (C), LED709.K (C), LED725.K (C), LED741.K (C), LED757.K (C), LED773.K (C), LED789.K (C), LED805.K (C), LED821.K (C), LED837.K (C), LED853.K (C), LED869.K (C), LED885.K (C), LED901.K (C), LED917.K (C), LED933.K (C), LED949.K (C), LED965.K (C), LED981.K (C), LED997.K (C), LED1013.K (C), LED1029.K (C), LED1045.K (C), LED1061.K (C), LED1077.K (C), LED1093.K (C), LED1109.K (C), LED1125.K (C), LED1141.K (C), LED1157.K (C), LED1173.K (C), LED1189.K (C), LED1205.K (C), LED1221.K (C), LED1237.K (C), LED1253.K (C), LED1269.K (C), R5.1
unnamed: LED6.K (C), LED22.K (C), LED38.K (C), LED54.K (C), LED70.K (C), LED86.K (C), LED102.K (C), LED118.K (C), LED134.K (C), LED150.K (C), LED166.K (C), LED182.K (C), LED198.K (C), LED214.K (C), LED230.K (C), LED246.K (C), LED262.K (C), LED278.K (C), LED294.K (C), LED310.K (C), LED326.K (C), LED342.K (C), LED358.K (C), LED374.K (C), LED390.K (C), LED406.K (C), LED422.K (C), LED438.K (C), LED454.K (C), LED470.K (C), LED486.K (C), LED502.K (C), LED518.K (C), LED534.K (C), LED550.K (C), LED566.K (C), LED582.K (C), LED598.K (C), LED614.K (C), LED630.K (C), LED646.K (C), LED662.K (C), LED678.K (C), LED694.K (C), LED710.K (C), LED726.K (C), LED742.K (C), LED758.K (C), LED774.K (C), LED790.K (C), LED806.K (C), LED822.K (C), LED838.K (C), LED854.K (C), LED870.K (C), LED886.K (C), LED902.K (C), LED918.K (C), LED934.K (C), LED950.K (C), LED966.K (C), LED982.K (C), LED998.K (C), LED1014.K (C), LED1030.K (C), LED1046.K (C), LED1062.K (C), LED1078.K (C), LED1094.K (C), LED1110.K (C), LED1126.K (C), LED1142.K (C), LED1158.K (C), LED1174.K (C), LED1190.K (C), LED1206.K (C), LED1222.K (C), LED1238.K (C), LED1254.K (C), LED1270.K (C), R6.1
unnamed: IC1.12 (O7), R7.2
unnamed: LED8.K (C), LED24.K (C), LED40.K (C), LED56.K (C), LED72.K (C), LED88.K (C), LED104.K (C), LED120.K (C), LED136.K (C), LED152.K (C), LED168.K (C), LED184.K (C), LED200.K (C), LED216.K (C), LED232.K (C), LED248.K (C), LED264.K (C), LED280.K (C), LED296.K (C), LED312.K (C), LED328.K (C), LED344.K (C), LED360.K (C), LED376.K (C), LED392.K (C), LED408.K (C), LED424.K (C), LED440.K (C), LED456.K (C), LED472.K (C), LED488.K (C), LED504.K (C), LED520.K (C), LED536.K (C), LED552.K (C), LED568.K (C), LED584.K (C), LED600.K (C), LED616.K (C), LED632.K (C), LED648.K (C), LED664.K (C), LED680.K (C), LED696.K (C), LED712.K (C), LED728.K (C), LED744.K (C), LED760.K (C), LED776.K (C), LED792.K (C), LED808.K (C), LED824.K (C), LED840.K (C), LED856.K (C), LED872.K (C), LED888.K (C), LED904.K (C), LED920.K (C), LED936.K (C), LED952.K (C), LED968.K (C), LED984.K (C), LED1000.K (C), LED1016.K (C), LED1032.K (C), LED1048.K (C), LED1064.K (C), LED1080.K (C), LED1096.K (C), LED1112.K (C), LED1128.K (C), LED1144.K (C), LED1160.K (C), LED1176.K (C), LED1192.K (C), LED1208.K (C), LED1224.K (C), LED1240.K (C), LED1256.K (C), LED1272.K (C), R8.1
unnamed: LED9.K (C), LED25.K (C), LED41.K (C), LED57.K (C), LED73.K (C), LED89.K (C), LED105.K (C), LED121.K (C), LED137.K (C), LED153.K (C), LED169.K (C), LED185.K (C), LED201.K (C), LED217.K (C), LED233.K (C), LED249.K (C), LED265.K (C), LED281.K (C), LED297.K (C), LED313.K (C), LED329.K (C), LED345.K (C), LED361.K (C), LED377.K (C), LED393.K (C), LED409.K (C), LED425.K (C), LED441.K (C), LED457.K (C), LED473.K (C), LED489.K (C), LED505.K (C), LED521.K (C), LED537.K (C), LED553.K (C), LED569.K (C), LED585.K (C), LED601.K (C), LED617.K (C), LED633.K (C), LED649.K (C), LED665.K (C), LED681.K (C), LED697.K (C), LED713.K (C), LED729.K (C), LED745.K (C), LED761.K (C), LED777.K (C), LED793.K (C), LED809.K (C), LED825.K (C), LED841.K (C), LED857.K (C), LED873.K (C), LED889.K (C), LED905.K (C), LED921.K (C), LED937.K (C), LED953.K (C), LED969.K (C), LED985.K (C), LED1001.K (C), LED1017.K (C), LED1033.K (C), LED1049.K (C), LED1065.K (C), LED1081.K (C), LED1097.K (C), LED1113.K (C), LED1129.K (C), LED1145.K (C), LED1161.K (C), LED1177.K (C), LED1193.K (C), LED1209.K (C), LED1225.K (C), LED1241.K (C), LED1257.K (C), LED1273.K (C), R9.1
unnamed: LED10.K (C), LED26.K (C), LED42.K (C), LED58.K (C), LED74.K (C), LED90.K (C), LED106.K (C), LED122.K (C), LED138.K (C), LED154.K (C), LED170.K (C), LED186.K (C), LED202.K (C), LED218.K (C), LED234.K (C), LED250.K (C), LED266.K (C), LED282.K (C), LED298.K (C), LED314.K (C), LED330.K (C), LED346.K (C), LED362.K (C), LED378.K (C), LED394.K (C), LED410.K (C), LED426.K (C), LED442.K (C), LED458.K (C), LED474.K (C), LED490.K (C), LED506.K (C), LED522.K (C), LED538.K (C), LED554.K (C), LED570.K (C), LED586.K (C), LED602.K (C), LED618.K (C), LED634.K (C), LED650.K (C), LED666.K (C), LED682.K (C), LED698.K (C), LED714.K (C), LED730.K (C), LED746.K (C), LED762.K (C), LED778.K (C), LED794.K (C), LED810.K (C), LED826.K (C), LED842.K (C), LED858.K (C), LED874.K (C), LED890.K (C), LED906.K (C), LED922.K (C), LED938.K (C), LED954.K (C), LED970.K (C), LED986.K (C), LED1002.K (C), LED1018.K (C), LED1034.K (C), LED1050.K (C), LED1066.K (C), LED1082.K (C), LED1098.K (C), LED1114.K (C), LED1130.K (C), LED1146.K (C), LED1162.K (C), LED1178.K (C), LED1194.K (C), LED1210.K (C), LED1226.K (C), LED1242.K (C), LED1258.K (C), LED1274.K (C), R10.1
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
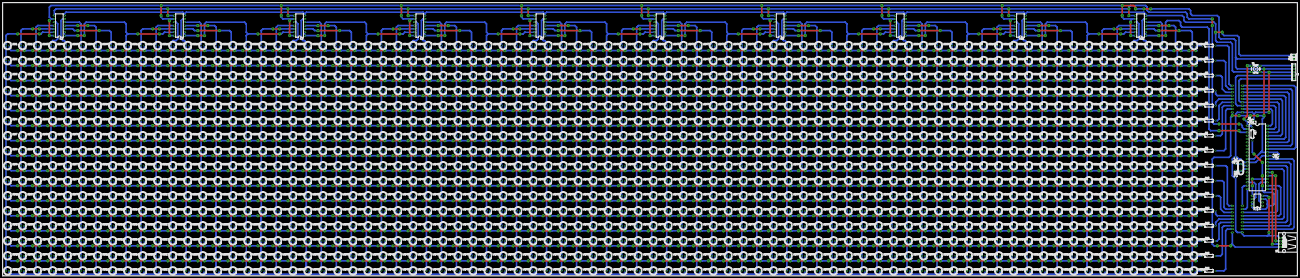
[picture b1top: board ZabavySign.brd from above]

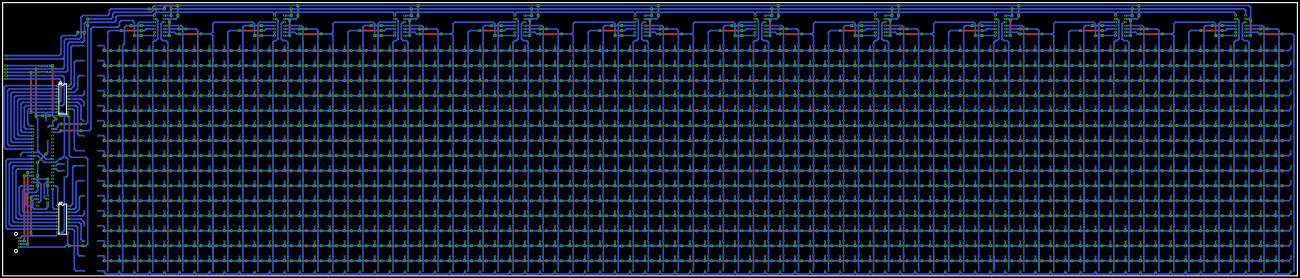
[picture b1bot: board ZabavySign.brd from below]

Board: 2 copper layers, 985.5 x 207.9 mm, 1320 parts (2 on the bottom side), 140 nets.

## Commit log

2022-05-22 Upload project
